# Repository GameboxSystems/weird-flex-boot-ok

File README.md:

# weird-flex-boot-ok
Quick solder flex cable and Pi Pico carrier and flex connecting PCB for Picoboot Gamecube mod.

Picoboot info can be found here: https://github.com/webhdx/PicoBoot

Webhdx has publically stated that the pins for Picoboot installation may change down the line to accommodate new features. Weird flex boot OK will be updated accordingly.

Big thank you to webhdx for their hard work on the Picoboot mod!

## PCB Build Specifications
PCB eagle files and gerbers are in the PCB folder. PCB thickness shall be 1.6mm.

BOM:

* J1 - 5 pin 1.0mm pitch FFC connector - TE Electronics - PN: 84952-5
* S1 - Slide switch SPST - CW Industries - PN: GF-123-0054

## QSB Flex Build Specifications
QSV Flex eagle files and gerbers are in the QSB-Flex folder. Flex cable thickness shall be 0.1mm with a plastic stiffner on the bottom of the flex with thickness of 0.2mm. Total thickness shall be 0.3mm with stiffner.

## Licensing
This project is licensed under GNU, feel free to do with the contents of this repo as you please. No guarantees or warranties assumed or provided.

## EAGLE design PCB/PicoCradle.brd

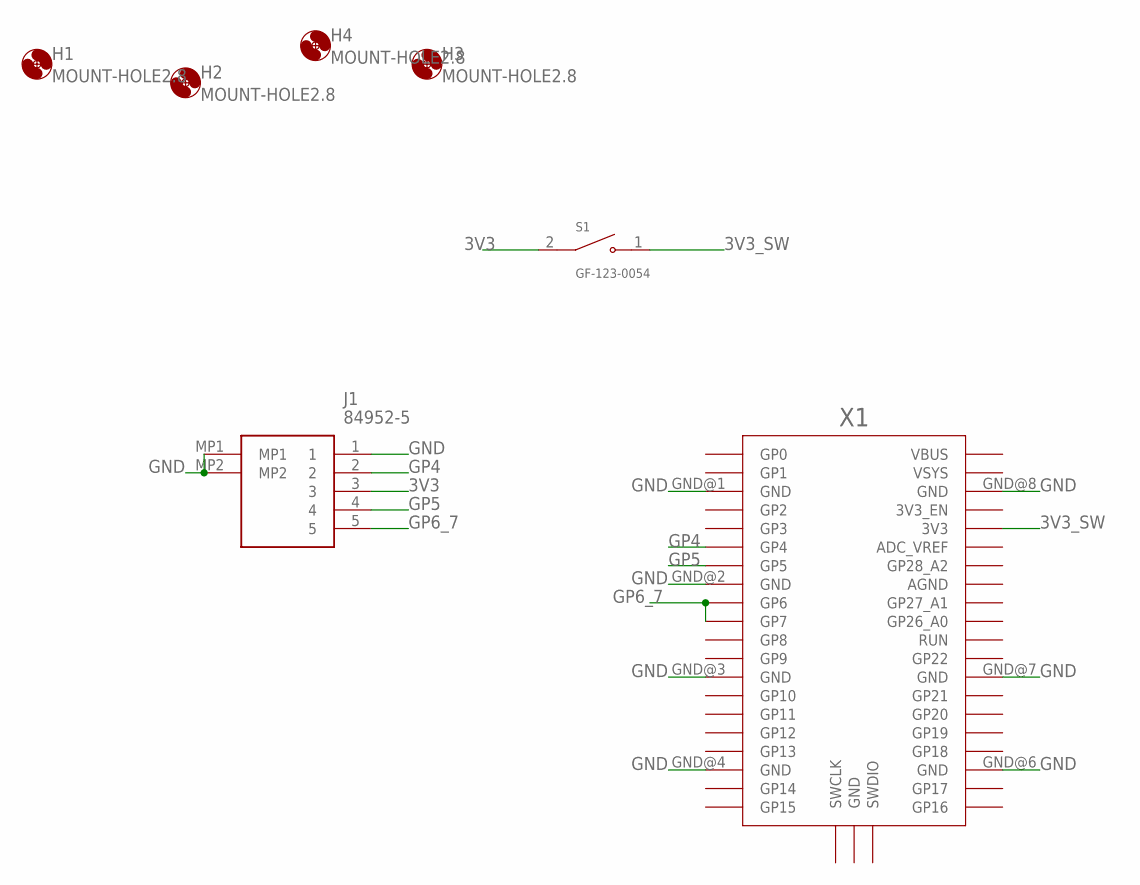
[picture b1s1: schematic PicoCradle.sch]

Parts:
H1, H2, H3, H4: MOUNT-HOLE2.8; 2,8
J1: 84952-5; 849525
S1: GF-123-0054; SW_GF-123-0054
X1: RPI_PICO_IG-SMD; RPI_PICO

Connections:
3V3: J1.3, S1.2
3V3_SW: S1.1, X1.3V3
GND: J1.1, J1.MP1, J1.MP2, X1.GND@1 (GND), X1.GND@2 (GND), X1.GND@3 (GND), X1.GND@4 (GND), X1.GND@6 (GND), X1.GND@7 (GND), X1.GND@8 (GND)
GP4: J1.2, X1.GP4
GP5: J1.4, X1.GP5
GP6_7: J1.5, X1.GP6, X1.GP7

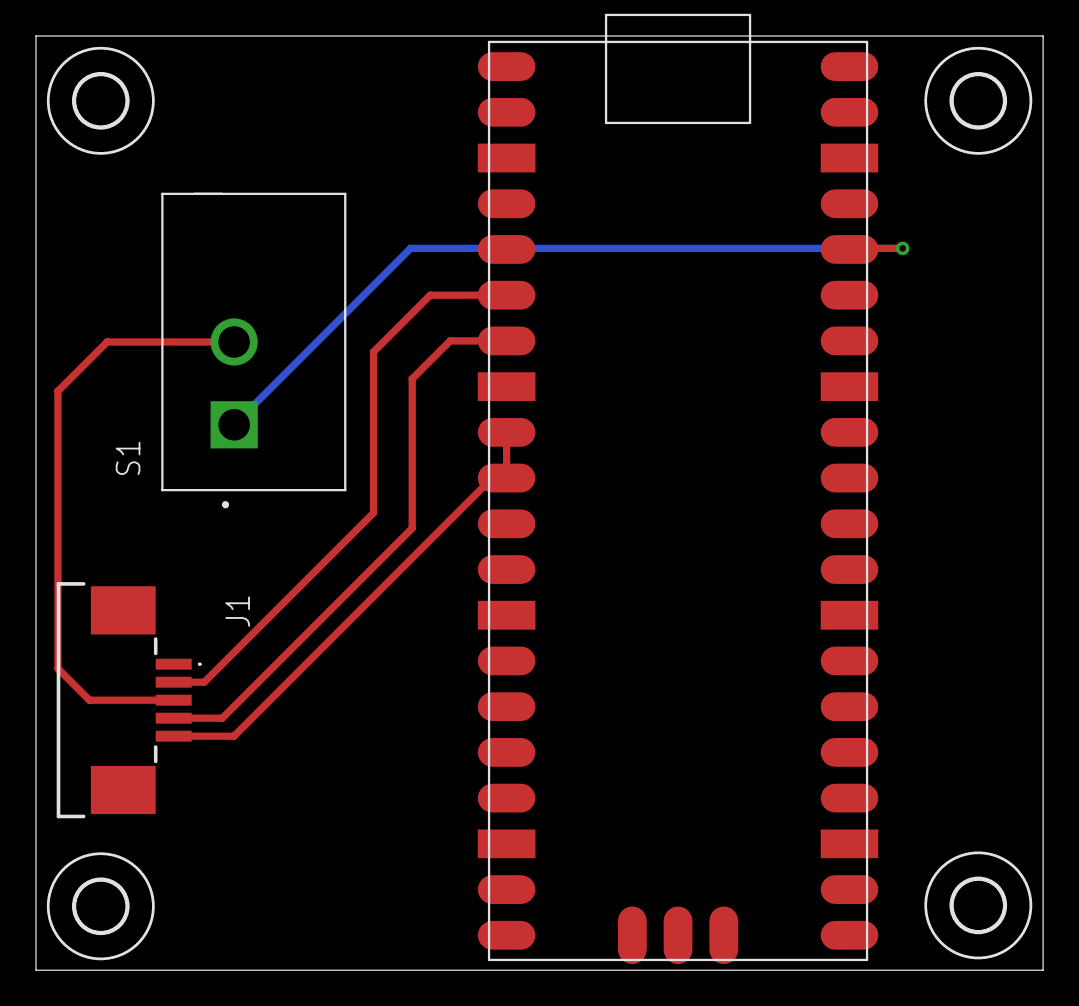
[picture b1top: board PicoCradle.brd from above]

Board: 2 copper layers, 56.0 x 51.9 mm, 8 parts (1 on the bottom side), 6 nets.

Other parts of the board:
U$1: SCREENSHOT_FROM_2022#08#13_22#09#53#PNG

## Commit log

2022-10-11 Added PCB and flex cable gerbers and files
2022-10-24 Added installation guide
